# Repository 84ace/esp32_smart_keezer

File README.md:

<!-- PROJECT SHIELDS -->
<!--
*** I'm using markdown "reference style" links for readability.
*** Reference links are enclosed in brackets [ ] instead of parentheses ( ).
*** See the bottom of this document for the declaration of the reference variables
*** for contributors-url, forks-url, etc. This is an optional, concise syntax you may use.
*** https://www.markdownguide.org/basic-syntax/#reference-style-links
-->
[![Contributors][contributors-shield]][contributors-url]
[![Forks][forks-shield]][forks-url]
[![Stargazers][stars-shield]][stars-url]
[![Issues][issues-shield]][issues-url]
[![MIT License][license-shield]][license-url]
[![LinkedIn][linkedin-shield]][linkedin-url]

<!-- PROJECT LOGO -->
<br />
<p align="center">

  <h3 align="center">ESP32 Smart Keezer</h3>

  <p align="center">
    Monitoring the beer flow!
    <br />
    <a href="https://github.com/84ace/esp32_smart_keezer/wiki"><strong>Explore the docs »</strong></a>
    <br />
    <br />
    <a href="https://github.com/84ace/esp32_smart_keezer/tree/master/board_images">Board Images</a>
    <a href="https://github.com/84ace/esp32_smart_keezer/issues">Report Bug</a>
    <a href="https://github.com/84ace/esp32_smart_keezer/issues">Request Feature</a>
  </p>
</p>

<!-- TABLE OF CONTENTS -->
<details open="open">
  <summary>Table of Contents</summary>
  <ol>
    <li>
      <a href="#about-the-project">About The Project</a>
      <ul>
        <li><a href="#main-features">Main Features</a></li>
        <li><a href="#whats-missing">What's Missing</a></li>
      </ul>
    </li>
    <li>
      <a href="#get-the-isolator">Get the Smart Keezer Gear</a>
    </li>
    <li><a href="#roadmap">Roadmap</a></li>
    <li><a href="#contributing">Contributing</a></li>
    <li><a href="#made-with">Made with</a></li>
    <li><a href="#license">License</a></li>
    <li><a href="#contact">Contact</a></li>
    <li><a href="#acknowledgements">Acknowledgements</a></li>
  </ol>
</details>

<!-- ABOUT THE PROJECT -->
## About The Project

[![ESP32 Smart Keezer][product-screenshot]](https://github.com/84ace/esp32_smart_keezer/raw/master/board_images/esp32_smart_keezer_front.jpg)

The ESP32 Smart Keezer was created so that we could monitor things inside the Keezer a bit better (so we knew when we were going to run out of beer), and also so we could have a cooler way of displaying what beers were on tap.

<!-- MAIN FEATURES -->
## Main Features:
* Web based  config (webserver)
* 10 channel flow meter
* Bluetooth (to update the tap handles)
* WiFi
* USB (for power and flashing/debug)

<!-- WHAT"S MISSING -->
## What's missing:
* Many many things

If you would like to contribute an app please contact me via the <a href="https://github.com/84ace/esp32_smart_keezer/tree/master/board_images">issues</a> page.

<!-- GETTING STARTED 
## Get the hardware

There are two ways to get started: 
* You can either take the easy(er) way and buy a pre-made unit from [here](https://placeholder.com/) 
* you can send the gerber files off to your favourite fab house, order the components, assemble the board and print the enclosure yourself.

Your choice!

-->

<!-- ROADMAP -->
## Roadmap

See the [open issues](https://github.com/84ace/esp32_smart_keezer/issues) for a list of proposed features (and known issues).

<!-- CONTRIBUTING -->
## Contributing

Contributions are what make the open source community such an amazing place to be learn, inspire, and create. Any contributions you make are **greatly appreciated**.

1. Fork the Project
2. Create your Feature Branch (`git checkout -b feature/AmazingFeature`)
3. Commit your Changes (`git commit -m 'Add some AmazingFeature'`)
4. Push to the Branch (`git push origin feature/AmazingFeature`)
5. Open a Pull Request

<!-- MADE WITH -->
## Made With:
* [KiCad - Electronic Design Automation Suite](https://kicad.org/)
* [Fusion360 - CAD Software](https://www.autodesk.com.au/products/fusion-360/overview)
* [JLCPCB - PCB Fabrication Manufacturer](https://jlcpcb.com/)

<!-- LICENSE -->
## License

Distributed under the MIT License. See `LICENSE` for more information.

<!-- CONTACT -->
## Contact

84ace - [@Racea_Quigg](https://twitter.com/@RaceaQuigg)

Project Link: [https://github.com/84ace/esp32_smart_keezer](https://github.com/84ace)

<!-- MARKDOWN LINKS & IMAGES -->
<!-- https://www.markdownguide.org/basic-syntax/#reference-style-links -->
[contributors-shield]: https://img.shields.io/github/contributors/84ace/esp32_smart_keezer.svg?style=for-the-badge
[contributors-url]: https://github.com/84ace/esp32_smart_keezer/graphs/contributors
[forks-shield]: https://img.shields.io/github/forks/84ace/esp32_smart_keezer.svg?style=for-the-badge
[forks-url]: https://github.com/84ace/esp32_smart_keezer/network/members
[stars-shield]: https://img.shields.io/github/stars/84ace/esp32_smart_keezer.svg?style=for-the-badge
[stars-url]: https://github.com/84ace/esp32_smart_keezer/stargazers
[issues-shield]: https://img.shields.io/github/issues/84ace/esp32_smart_keezer.svg?style=for-the-badge
[issues-url]: https://github.com/84ace/esp32_smart_keezer/issues
[license-shield]: https://img.shields.io/github/license/84ace/esp32_smart_keezer.svg?style=for-the-badge
[license-url]: https://github.com/84ace/esp32_smart_keezer/blob/master/LICENSE.txt
[linkedin-shield]: https://img.shields.io/badge/-LinkedIn-black.svg?style=for-the-badge&logo=linkedin&colorB=555
[linkedin-url]: https://www.linkedin.com/in/acea-quigg-2007036b/
[product-screenshot]: board_images/esp32_smart_keezer_front.jpg

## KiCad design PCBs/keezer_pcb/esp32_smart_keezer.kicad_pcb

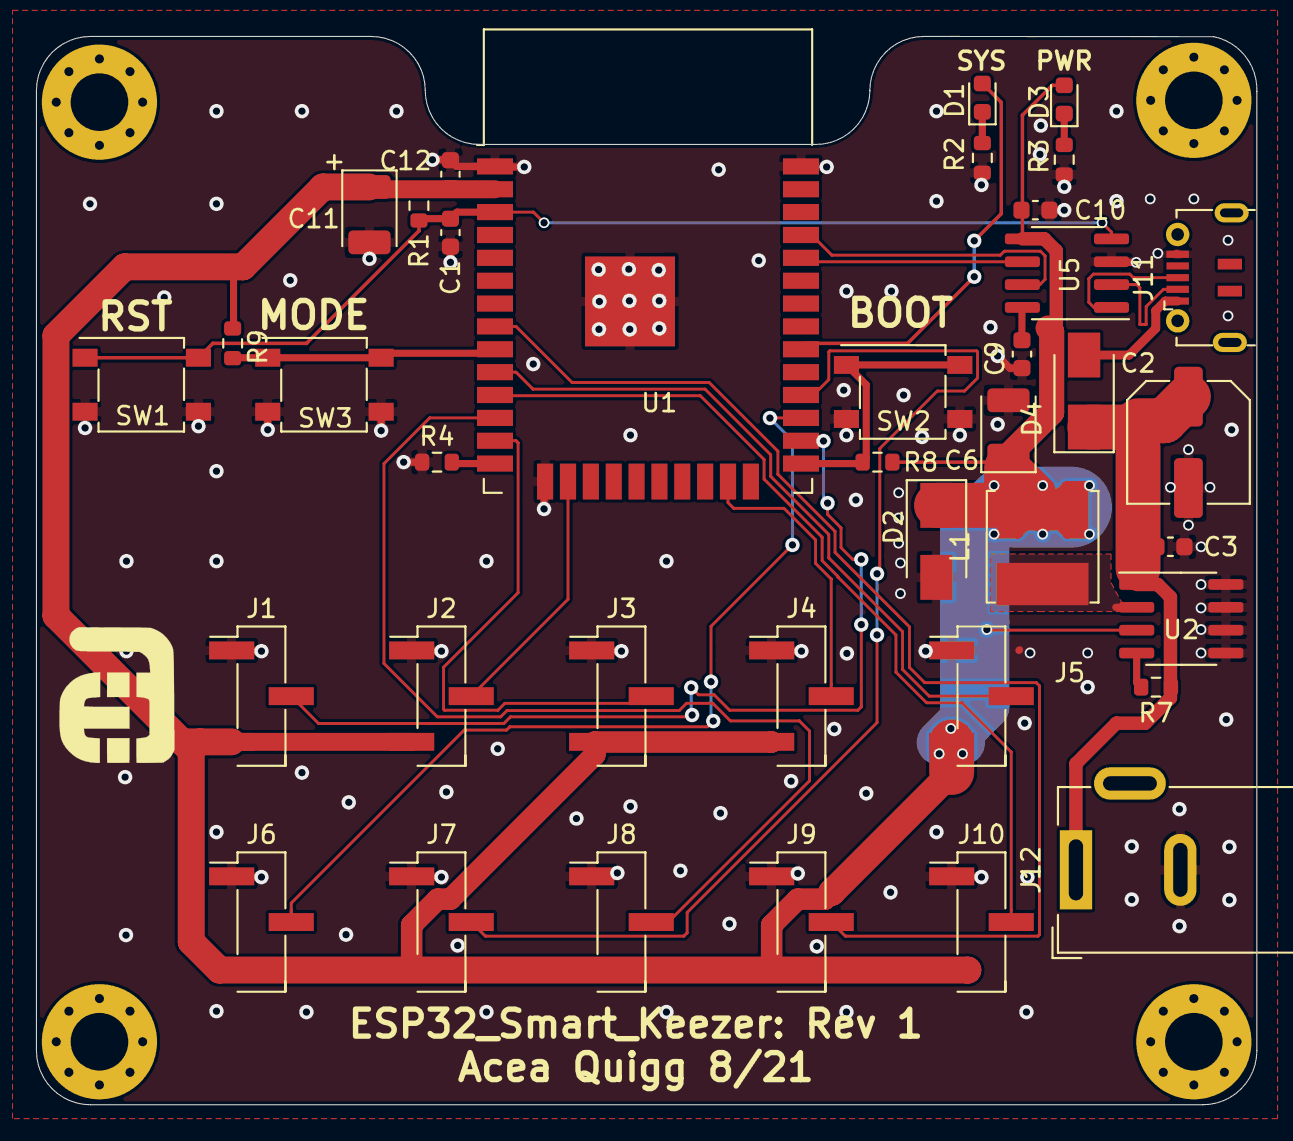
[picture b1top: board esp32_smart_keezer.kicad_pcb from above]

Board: 2 copper layers, 67.8 x 59.3 mm, 43 parts (0 on the bottom side), 28 nets.

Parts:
C1, C3, C9, C10, C12: 100n; C_0603_1608Metric
C2: 220uF; C_Elec_6.3x7.7
C6: 220uF; CP_EIA-3528-15_AVX-H
C11: 1uF; CP_EIA-3528-21_Kemet-B
D1: MAIN LED; LED_0603_1608Metric
D2, D4: SS34; D_SMA
D3: POWER LED; LED_0603_1608Metric
H1, H1#2, H1#3, H1#4: MountingHole_3.2mm_M3_Pad_Via
J1, J2, J3, J4, J5, J6, J7, J8, J9, J10: Conn_01x03_Male; PinHeader_1x03_P2.54mm_Vertical_SMD_Pin1Left
J11: USB_B_Micro; USB_Micro_SHOU-HAN-MicroXNJ_C404969_Horizontal
J12: Barrel_Jack_MountingPin; BarrelJack_Wuerth_6941xx301002
L1: 47uH; L_Bourns_SRN6045TA
R1, R4, R8, R9: 10k; R_0603_1608Metric
R2, R3: 3.6k; R_0603_1608Metric
R7: 1M; R_0603_1608Metric
Ref**: Val**; aces_electronics_small_front
SW1, SW2, SW3: C492887; TS4550TP
U1: ESP32-WROOM-32D; ESP32-WROOM-32
U2: XL1509_SOP8; SOIC-8_3.9x4.9mm_P1.27mm
U5: CH340N; SOIC-8_3.9x4.9mm_P1.27mm

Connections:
5V: D4.2, J11.1
+3V3: C6.1, C10.1, C11.1, C12.1, D2.1, D3.2, J1.3, J2.3, J3.3, J4.3, J5.3, J6.3, J7.3, J8.3, J9.3, J10.3, L1.2, R1.1, R8.1, R9.2, U1.2, U2.3, U5.5
BOOT: R8.2, SW2.1, U1.25
D+: J11.3, U5.1
D-: J11.2, U5.2
GND: C1.2, C2.2, C3.2, C6.2, C9.2, C10.2, C11.2, C12.2, D2.2, J1.1, J2.1, J3.1, J4.1, J5.1, J6.1, J7.1, J8.1, J9.1, J10.1, J11.5, J12.2, R2.2, R3.2, R4.1, SW1.2, SW2.2, SW3.2, U1.1, U1.15, U1.38, U1.39, U2.5, U2.6, U2.7, U2.8, U5.3
MODE: R9.1, SW3.1, U1.9
unnamed: C9.1, U5.8
unnamed: D1.1, R2.1
unnamed: D3.1, R3.1
unnamed: L1.1, U2.2
unnamed: R4.2, U1.14
unnamed: R7.2, U2.4
P1: J1.2, U1.26
P2: J2.2, U1.16
P3: J3.2, U1.13
P4: J4.2, U1.23
P5: J5.2, U1.10
P6: J10.2, U1.11
P7: J8.2, U1.12
P8: J9.2, U1.8
P9: J6.2, U1.27
P10: J7.2, U1.28
RST: C1.1, R1.2, SW1.1, U1.3, U5.4
RXD: U1.34, U5.6
SYS_OK_LED: D1.2, U1.30
TXD: U1.35, U5.7
VIN: C2.1, C3.1, D4.1, J12.1, R7.1, U2.1

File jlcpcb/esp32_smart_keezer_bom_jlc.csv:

"Comment","Designator","Footprint","LCSC Part #"
"220uF","C2","C_Elec_6.3x7.7","C371974"
"220uF","C6","CP_EIA-3528-15_AVX-H","C30242"
"1uF","C11","CP_EIA-3528-21_Kemet-B","C169224"
"100n","C12,C1,C10,C9,C3","C_0603_1608Metric","C14663"
"MAIN LED","D1","LED_0603_1608Metric","C2286"
"POWER LED","D3","LED_0603_1608Metric","C2286"
"SS34","D4,D2","D_SMA","C8678"
"Conn_01x03_Male","J1,J4,J5,J2,J3,J10,J8,J9,J6,J7","PinHeader_1x03_P2.54mm_Vertical_SMD_Pin1Left","C780061"
"USB_B_Micro","J11","USB_Micro_SHOU-HAN-MicroXNJ_C404969_Horizontal","C404969"
"Barrel_Jack_MountingPin","J12","BarrelJack_Wuerth_6941xx301002","C136744"
"47uH","L1","L_Bourns_SRN6045TA","C36414"
"10k","R1,R8,R4,R9","R_0603_1608Metric","C25804"
"3.6k","R2,R3","R_0603_1608Metric","C22980"
"1M","R7","R_0603_1608Metric","C22935"
"C492887","SW1,SW2,SW3","TS4550TP","C492887"
"ESP32-WROOM-32D","U1","ESP32-WROOM-32","C473012"
"XL1509_SOP8","U2","SOIC-8_3.9x4.9mm_P1.27mm","C2681226"
"CH340N","U5","SOIC-8_3.9x4.9mm_P1.27mm","C506813"

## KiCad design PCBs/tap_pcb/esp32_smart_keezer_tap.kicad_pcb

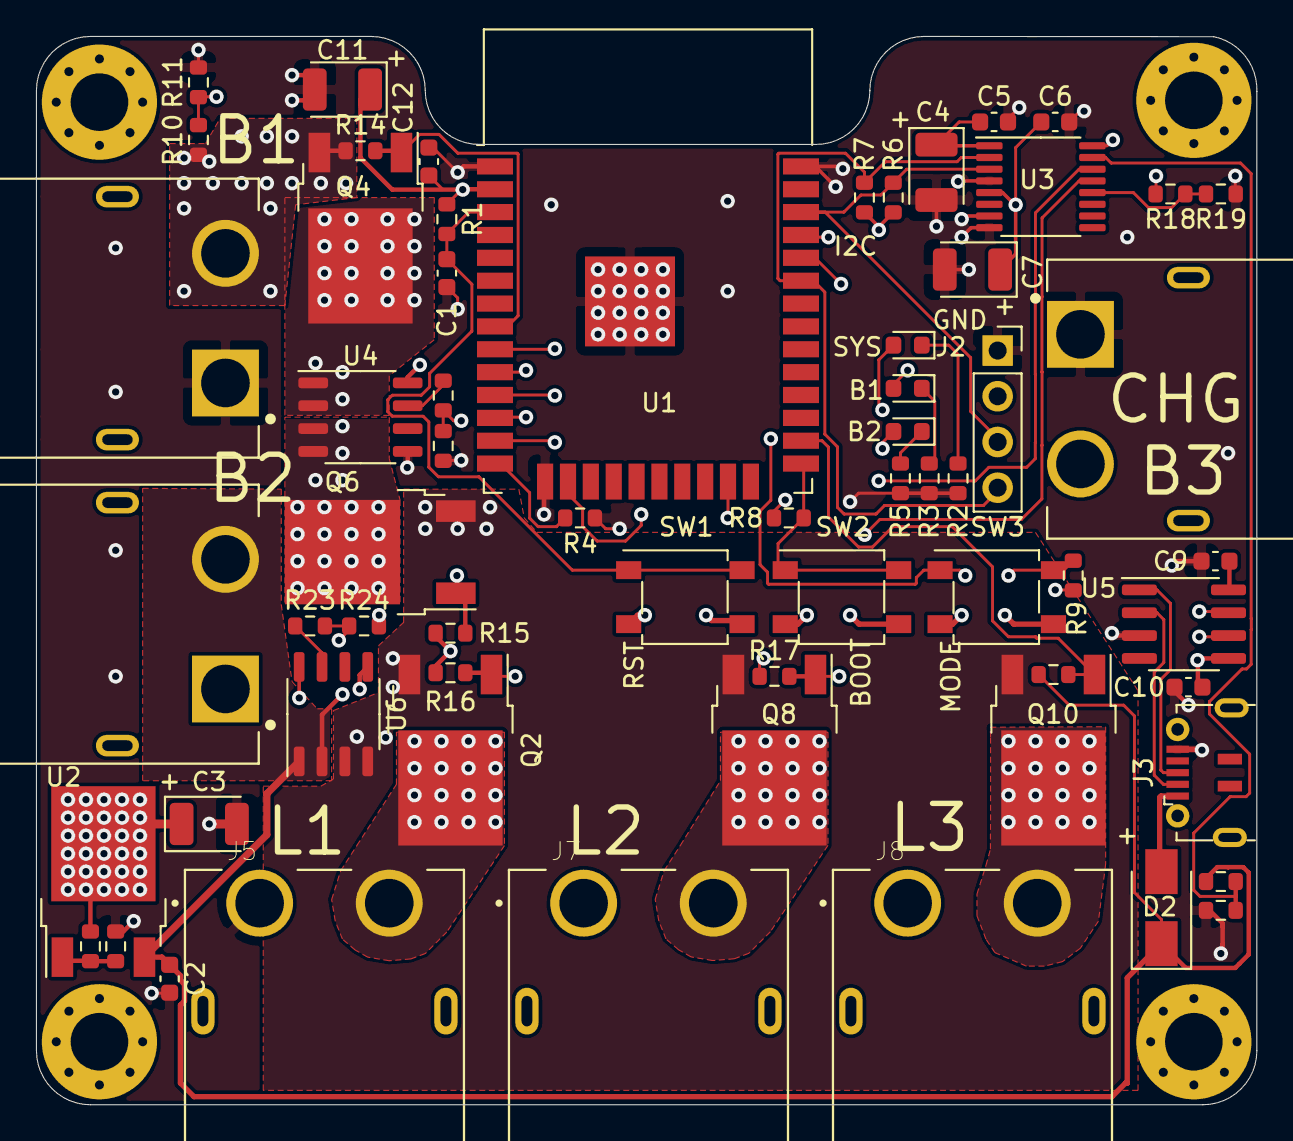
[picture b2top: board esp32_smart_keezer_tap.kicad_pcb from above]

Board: 4 copper layers, 67.8 x 59.3 mm, 67 parts (0 on the bottom side), 42 nets.

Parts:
C1, C2, C5, C6, C9, C10, C12: 100n; C_0603_1608Metric
C3, C4, C7, C11: 1uF; CP_EIA-3528-21_Kemet-B
D1, D3, D4: MAIN LED; LED_0603_1608Metric
D2: SS14; D_SMA
H1, H1#2, H1#3, H1#4: MountingHole_3.2mm_M3_Pad_Via
J1: BATT1; AMASS_XT60PW-M
J2: Conn_01x04_Female; PinSocket_1x04_P2.54mm_Vertical
J3: USB_B_Micro; USB_Micro_SHOU-HAN-MicroXNJ_C404969_Horizontal
J4: BATT2; AMASS_XT60PW-M
J5: LOAD1; AMASS_XT60PW-F
J6: CHGR; AMASS_XT60PW-M
J7: LOAD2; AMASS_XT60PW-F
J8: LOAD3; AMASS_XT60PW-F
Q2, Q4, Q6, Q8, Q10: AP6679GH-HF; TO-252-2
R1, R4, R8, R9, R19, R22, R24: 11k; R_0603_1608Metric
R2, R3, R5, R6, R7, R18, R21, R23: 3.6k; R_0603_1608Metric
R10, R12, R14, R15, R16, R17, R20: 200k; R_0603_1608Metric
R11, R13: 33k; R_0603_1608Metric
R25: 200R; R_0603_1608Metric
R26: 330R; R_0603_1608Metric
SW1, SW2, SW3: C492887; TS4550TP
U1: ESP32-WROOM-32D; ESP32-WROOM-32
U2: LM317AG-TN3-R; TO-252-2
U3: ADC128D818; TSSOP-16_4.4x5mm_P0.65mm
U4, U6: CC6903SO-30A; SOP-8_3.9x4.9mm_P1.27mm
U5: CH330N; SOIC-8_3.9x4.9mm_P1.27mm

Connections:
3v3VD: R18.2, R19.1, U3.12
5V: D2.2, J3.1
+3V3: C3.1, C6.1, C7.1, C10.1, C11.1, C12.1, J2.2, R1.1, R6.1, R7.1, R8.1, R9.2, R18.1, R25.1, U1.2, U2.2, U3.5, U4.8, U5.5, U6.8
B1C: J6.2, Q4.2, U4.1, U4.2
B1CM: R21.1, U4.7
B1CVD: R21.2, R22.1, U3.14
B1ON: Q4.1, R14.2, U1.8
B1VD: R10.2, R11.1, U3.16
B1VM: J1.2, Q4.3, R10.1, R14.1
B1_LED: D3.2, U1.13
B2C: Q2.3, Q6.3, Q8.3, Q10.3, U6.3, U6.4
B2CM: R23.1, U6.7
B2CVD: R23.2, R24.1, U3.13
B2ON: Q6.1, R15.2, U1.11
B2VD: R12.2, R13.1, U3.15
B2VM: C2.1, D2.1, J4.2, R12.1, R15.1, R16.1, R17.1, R20.1, U2.3, U6.1, U6.2
B2_LED: D4.2, U1.10
BOOT: R8.2, SW2.1, U1.25
COM: Q6.2, U4.3, U4.4
D+: J3.3, U5.1
D-: J3.2, U5.2
GND: C1.2, C2.2, C3.2, C4.2, C5.2, C6.2, C7.2, C9.2, C10.2, C11.2, C12.2, J1.1, J2.1, J3.5, J4.1, J5.1, J6.1, J7.1, J8.1, R2.2, R3.2, R4.1, R5.2, R11.2, R13.2, R19.2, R22.2, R24.2, R26.2, SW1.2, SW2.2, SW3.2, U1.1, U1.15, U1.38, U1.39, U3.4, U3.7, U3.8, U4.5, U5.3, U6.5
L1ON: Q2.1, R16.2, U1.23
L2ON: Q8.1, R17.2, U1.16
L3ON: Q10.1, R20.2, U1.26
LOAD1: J5.2, Q2.2
LOAD2: J7.2, Q8.2
LOAD3: J8.2, Q10.2
MODE: R9.1, SW3.1, U1.9
unnamed: C4.1, C5.1, U3.1
unnamed: C9.1, U5.8
unnamed: D1.1, R2.1
unnamed: D3.1, R3.1
unnamed: D4.1, R5.1
unnamed: R4.2, U1.14
unnamed: R25.2, R26.1, U2.1
RST: C1.1, R1.2, SW1.1, U1.3
RXD: U1.34, U5.6
SCL: J2.3, R6.2, U1.36, U3.3
SDA: J2.4, R7.2, U1.33, U3.2
SYS_OK_LED: D1.2, U1.12
TXD: U1.35, U5.7

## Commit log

2021-03-08 added gitignore
2021-08-29 Rev 1 - WIP
2021-09-04 REV 1 - off to JLCPCB
2021-09-18 kegtastic software early WIP
2021-09-19 WIP - /get broken
2021-09-20 Settings page working
2021-09-20 WIP - getting there, names kinda updating
2021-09-21 MVP complete - alpha release 1
2021-09-21 Cleaning up
